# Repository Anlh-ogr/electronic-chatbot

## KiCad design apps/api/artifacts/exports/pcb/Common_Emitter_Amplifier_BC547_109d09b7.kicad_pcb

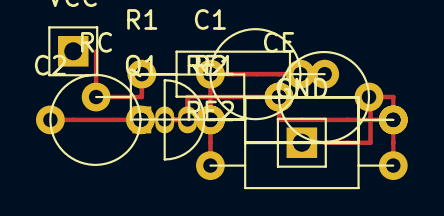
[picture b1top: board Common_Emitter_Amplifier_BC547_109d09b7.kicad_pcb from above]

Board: 2 copper layers, 11 parts (0 on the bottom side), 6 nets.

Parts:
C1, C2: CAPACITOR; C_Disc_D5.0mm_W2.5mm_P5.00mm
CE: CAPACITOR; C_Radial_D5.0mm_H11.0mm_P2.00mm
GND: POWER_SYMBOL; N/A
Q1: BJT_NPN; TO-92_Inline
R1, R2: RESISTOR; R_Axial_DIN0207_L6.3mm_D2.5mm_P10.16mm_Horizontal
RC: RESISTOR; R_Axial_DIN0207_L6.3mm_D2.5mm_P10.16mm_Horizontal
RE1, RE2: RESISTOR; R_Axial_DIN0207_L6.3mm_D2.5mm_P10.16mm_Horizontal
VCC: POWER_SYMBOL; N/A

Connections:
0: CE.2, GND.1, R2.2, RE2.2
BASE: C1.2, Q1.2, R1.2, R2.1
BYPASS: CE.1, RE1.2
COLLECTOR: C2.1, Q1.3, RC.2
EMITTER: Q1.1, RE1.1, RE2.1
VCC: R1.1, RC.1, VCC.1

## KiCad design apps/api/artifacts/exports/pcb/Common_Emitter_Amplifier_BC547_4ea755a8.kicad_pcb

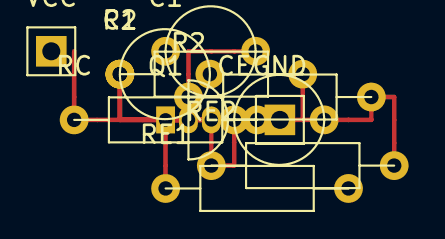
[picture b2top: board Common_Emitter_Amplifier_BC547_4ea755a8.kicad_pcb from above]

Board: 2 copper layers, 11 parts (0 on the bottom side), 5 nets.

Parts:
C1, C2: CAPACITOR; C_Disc_D5.0mm
CE: CAPACITOR; C_Disc_D5.0mm
GND: POWER_SYMBOL; None
Q1: BJT_NPN; TO-92_Inline
R1, R2: RESISTOR; R_Axial_DIN0207
RC: RESISTOR; R_Axial_DIN0207
RE1, RE2: RESISTOR; R_Axial_DIN0207
VCC: POWER_SYMBOL; None

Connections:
0: CE.2, GND.1, R2.2, RE2.2
BASE: C1.2, Q1.2, R1.1, R2.1
COLLECTOR: C2.1, Q1.3, RC.2
EMITTER: CE.1, Q1.1, RE1.1, RE2.1
VCC: R1.2, RC.1, VCC.1

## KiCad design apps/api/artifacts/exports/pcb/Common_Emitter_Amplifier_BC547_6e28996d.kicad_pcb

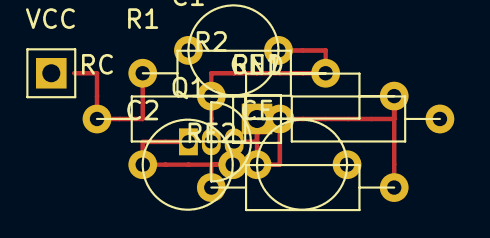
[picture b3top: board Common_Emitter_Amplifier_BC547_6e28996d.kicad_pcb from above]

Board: 2 copper layers, 11 parts (0 on the bottom side), 5 nets.

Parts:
C1, C2: CAPACITOR; C_Disc_D5.0mm
CE: CAPACITOR; C_Disc_D5.0mm
GND: POWER_SYMBOL; N/A
Q1: BJT_NPN; TO-92_Inline
R1, R2: RESISTOR; R_Axial_DIN0207
RC: RESISTOR; R_Axial_DIN0207
RE1, RE2: RESISTOR; R_Axial_DIN0207
VCC: POWER_SYMBOL; N/A

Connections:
0: GND.1, R2.2, RE2.2
BASE: C1.2, Q1.2, R1.2, R2.1
COLLECTOR: C2.1, Q1.1, RC.2
EMITTER: CE.1, Q1.3, RE1.1, RE2.1
VCC: R1.1, RC.1, VCC.1

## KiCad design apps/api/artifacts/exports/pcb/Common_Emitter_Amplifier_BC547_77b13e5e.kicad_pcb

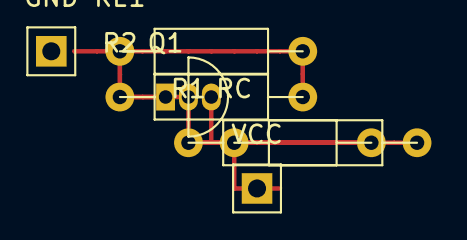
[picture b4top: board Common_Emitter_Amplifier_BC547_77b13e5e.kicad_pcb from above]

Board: 2 copper layers, 7 parts (0 on the bottom side), 5 nets.

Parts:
GND: POWER_SYMBOL; None
Q1: BJT_NPN; TO-92_Inline
R1, R2: RESISTOR; R_Axial_DIN0207
RC: RESISTOR; R_Axial_DIN0207
RE1: RESISTOR; R_Axial_DIN0207
VCC: POWER_SYMBOL; None

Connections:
0: GND.1, R2.2, RE1.2
BASE: Q1.2, R1.2, R2.1
COLLECTOR: Q1.3, RC.2
EMITTER: Q1.1, RE1.1
VCC: R1.1, RC.1, VCC.1
